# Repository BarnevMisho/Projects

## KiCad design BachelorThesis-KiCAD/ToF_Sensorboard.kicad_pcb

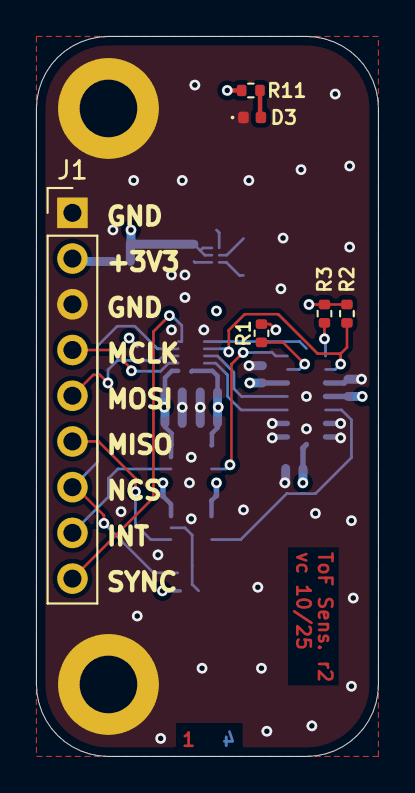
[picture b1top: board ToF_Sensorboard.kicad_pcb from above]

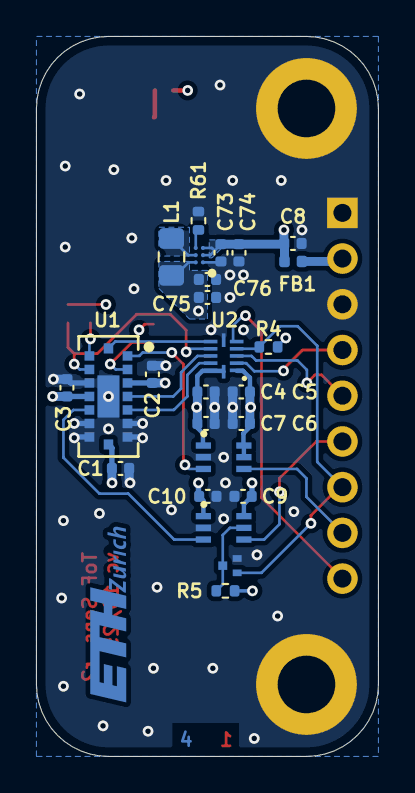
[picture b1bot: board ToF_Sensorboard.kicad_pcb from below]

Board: 4 copper layers, 19.0 x 40.0 mm, 34 parts (26 on the bottom side), 22 nets.

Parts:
A1: eth-zurich_2mm
C1, C2, C4, C5, C6, C7, C9, C10: 100n; C_0402_1005Metric
C3, C8: 4u7; C_0402_1005Metric
C73, C74, C75, C76: 10u; C_0402_1005Metric
D3: LED GREEN; LED_0402_1005Metric
FB1: BLM15AG102SH1J; L_0402_1005Metric
H1, H2: MountingHole_Pad; MountingHole_3.2mm_M3_DIN965_Pad
J1: Conn_01x09_Pin; PinHeader_1x09_P2.54mm_Vertical
L1: 2u2; L_0805_2012Metric_Pad1.15x1.40mm_HandSolder
Q1: RUM001L02T2CL
R1, R2, R3, R4, R5: 47k; R_0402_1005Metric
R11: 680R; R_0402_1005Metric
R61: 0R; R_0402_1005Metric
U1: VL53L8CXV0GC/1; VL53L8CXV0GC
U2: TXU0104RUTR; PQFP12_RUT_TEX-L
U3, U4: TXU0101DCKR; SC70-6_DCK_TEX
U20: TPS62840YBGR

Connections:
+1V8: C1.1, C2.1, C4.1, C7.1, C10.1, C75.1, C76.1, L1.2, R1.1, R2.1, R3.1, U1.A3 (IOVDD), U1.B7 (CORE_1V8), U2.11 (VCCB), U2.12 (OE), U3.1 (VCCA), U4.1 (VCCA), U20.A2 (VOS)
+3.3VA: C3.1, C5.1, C6.1, C8.1, C9.1, C73.1, C74.1, FB1.2, R4.1, R5.1, R11.1, U1.C4 (AVDD), U2.1 (VCCA), U3.5 (OE), U3.6 (VCCB), U4.6 (VCCB), U20.B1 (VIN), U20.C1 (EN)
/INT: J1.8, U3.4 (BY)
/INT_1V8: U1.A1 (GPIO1/INT), U3.3 (A)
/MCLK: J1.4, U2.2 (A1)
/MCLK_1V8: U1.A5 (SCL/MCLK), U2.10 (B1Y)
/MISO: J1.6, U4.4 (BY)
/MISO_1V8: U1.C5 (MISO), U4.3 (A)
/MOSI: J1.5, U2.3 (A2)
/MOSI_1V8: U1.A4 (SDA/MOSI), U2.9 (B2Y)
/NCS: J1.7, Q1.1 (Gate), R4.2, U2.4 (A3)
/NCS_1V8: R2.2, U1.C2 (NCS), U2.8 (B3Y)
/SYNC: J1.9, U2.5 (A4)
/SYNC_1V8: U1.B1 (GPIO2/SYNC), U2.7 (B4Y)
GND: C1.2, C2.2, C3.2, C4.2, C5.2, C6.2, C7.2, C8.2, C9.2, C10.2, C73.2, C74.2, C75.2, C76.2, D3.1 (K), H1.1, H2.1, J1.1, J1.3, Q1.2 (Source), R61.2, U1.A6 (RSVD1), U1.A7 (RSVD2), U1.B4 (GND_PAD), U1.C3 (GND), U1.C6 (RSVD3), U1.C7 (GND), U2.6 (GND), U3.2 (GND), U4.2 (GND), U20.A1 (GND)
unnamed: D3.2 (A), R11.2
unnamed: FB1.1, J1.2
unnamed: Q1.3 (Drain), R5.2, U4.5 (OE)
unnamed: R1.2, U1.A2 (LPN)
unnamed: R3.2, U1.C1 (SPI_I2C_N)
unnamed: L1.1, U20.B2 (SW)
unnamed: R61.1, U20.C2 (VSET)

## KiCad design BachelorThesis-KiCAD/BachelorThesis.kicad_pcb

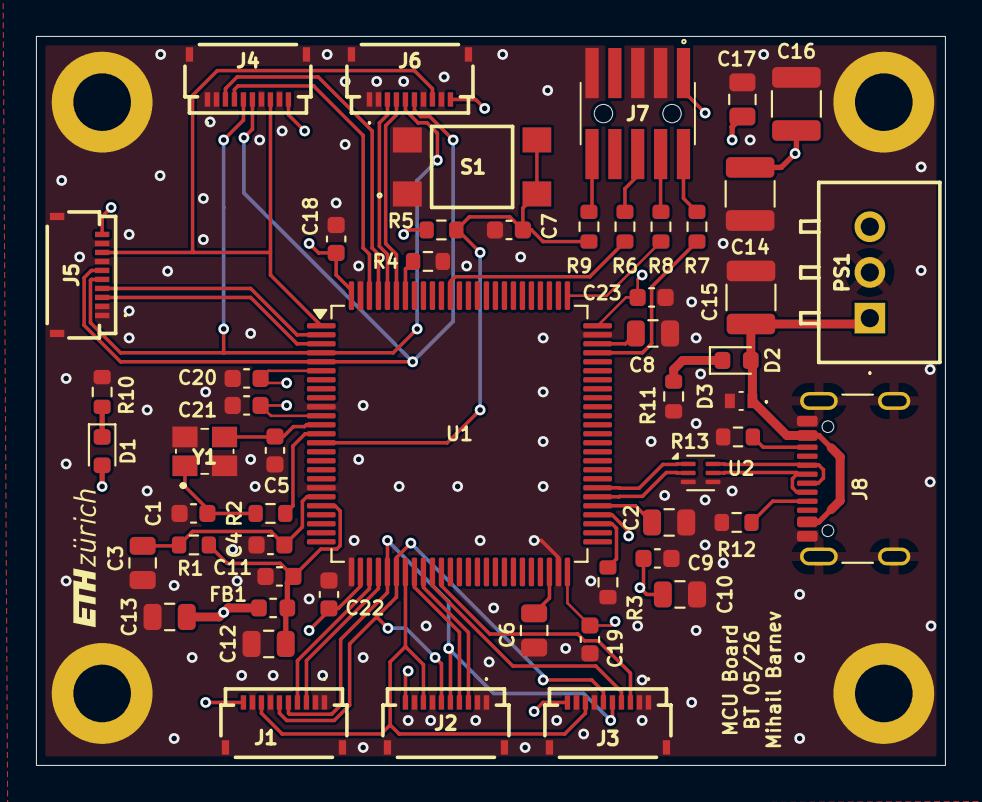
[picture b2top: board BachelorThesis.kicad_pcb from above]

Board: 4 copper layers, 50.5 x 40.5 mm, 57 parts (0 on the bottom side), 47 nets.

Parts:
C1, C5: 10p; C_0603_1608Metric
C2, C6, C8: 2.2u; C_0805_2012Metric
C3, C10, C12, C13: 1u; C_0805_2012Metric
C4, C7, C9, C11, C18, C19, C20, C21, C22, C23: 100n; C_0603_1608Metric
C14, C16: 47u; C_1210_3225Metric
C15: 10u; C_1210_3225Metric
C17: 4.7u; C_0805_2012Metric
D1, D2: LED; LED_0603_1608Metric
D3: ESDA7P60-1U1M; ESDA7P601U1M
FB1: FCM1608KF-601T03 -0603 1608 Metric; L_0603_1608Metric
H1, H2, H3, H4: MountingHole_Pad; MountingHole_3.2mm_M3_DIN965_Pad
J1, J2, J3, J4, J5, J6: FH34SRJ-10S-0.5SH_50_; FH34SRJ10S05SH50
J7: Conn_ARM_JTAG_SWD_10; FTSH-105-XX-YYY-DV-K-A
J8: USB_C_Receptacle_USB2.0_16P; USB_C_Receptacle_GCT_USB4105-xx-A_16P_TopMnt_Horizontal
PS1: TPSM84203EAB
R1, R6, R7, R8, R9: 33ohm; R_0603_1608Metric
R2, R4: 0Ω; R_0603_1608Metric
R3: 3k±1%; R_0603_1608Metric
R5, R12, R13: 5k1±1%; R_0603_1608Metric
R10, R11: 470ohm; R_0603_1608Metric
S1: TL3305AF160QG
U1: STM32F723VET6; LQFP-100_14x14mm_P0.5mm
U2: ECMF02-2AMX6; ST_UQFN-6L_1.5x1.7mm_P0.5mm
Y1: ABM8W-25.0000MHZ-8-D1X-T3; ABM8W480000MHZ6D1XT3

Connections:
/MCU_CORE/HSE_IN: C5.1 (+), U1.12 (PH0), Y1.3 (X2)
/MCU_CORE/HSE_OUT: R2.1 (+), U1.13 (PH1)
/MCU_CORE/INT_1_1: J1.3, U1.29 (PA5)
/MCU_CORE/INT_1_2: J2.3, U1.34 (PB0)
/MCU_CORE/INT_1_3: J3.3, U1.36 (PB2)
/MCU_CORE/INT_4_1: J4.3, U1.97 (PE0)
/MCU_CORE/INT_4_2: J5.3, U1.3 (PE4)
/MCU_CORE/INT_4_3: J6.3, U1.96 (PB9)
/MCU_CORE/NCS_1_1: J1.4, U1.28 (PA4)
/MCU_CORE/NCS_1_2: J2.4, U1.33 (PC5)
/MCU_CORE/NCS_1_3: J3.4, U1.35 (PB1)
/MCU_CORE/NCS_4_1: J4.4, U1.98 (PE1)
/MCU_CORE/NCS_4_2: J5.4, U1.2 (PE3)
/MCU_CORE/NCS_4_3: J6.4, U1.95 (PB8)
/MCU_CORE/SPI1_MISO: J1.5, J2.5, J3.5, U1.30 (PA6)
/MCU_CORE/SPI1_MOSI: J1.6, J2.6, J3.6, U1.31 (PA7)
/MCU_CORE/SPI1_SCK: J1.8, J2.8, J3.8, U1.32 (PC4)
/MCU_CORE/SPI4_MISO: J4.5, J5.5, J6.5, U1.4 (PE5)
/MCU_CORE/SPI4_MOSI: J4.6, J5.6, J6.6, U1.5 (PE6)
/MCU_CORE/SPI4_SCK: J4.8, J5.8, J6.8, U1.1 (PE2)
/MCU_CORE/SWD_CLK: J7.4 (SWCLK/TCK), R8.2 (-)
/MCU_CORE/SWD_DIO: J7.2 (SWDIO/TMS), R7.2 (-)
/MCU_CORE/SWD_NRST: C7.2 (-), R5.2, R9.1 (+), S1.2, S1.4, U1.14 (NRST)
/MCU_CORE/SWD_SWO: J7.6 (SWO/TDO), R6.2 (-)
/MCU_CORE/USBC_N: J8.A7 (D-), J8.B7 (D-), U2.5 (D-_out)
/MCU_CORE/USBC_P: J8.A6 (D+), J8.B6 (D+), U2.6 (D+_out)
/MCU_CORE/USB_HS_N: U1.56 (PB14), U2.2 (D-_in)
/MCU_CORE/USB_HS_P: U1.57 (PB15), U2.1 (D+_in)
GND: C1.2 (-), C2.2 (-), C3.2 (-), C4.2 (-), C5.2 (-), C6.2 (-), C7.1 (+), C8.2 (-), C9.2 (-), C10.2 (-), C11.2 (-), C12.2 (-), C13.2 (-), C14.2 (-), C15.1 (+), C16.2 (-), C17.2 (-), C18.2 (-), C19.2 (-), C20.2 (-), C21.2 (-), C22.2 (-), C23.2 (-), D3.2 (A), H1.1, H2.1, H3.1, H4.1, J1.1, J1.2, J1.7, J1.9, J1.11 (MP1), J1.12 (MP2), J2.1, J2.2, J2.7, J2.9, J2.11 (MP1), J2.12 (MP2), J3.1, J3.2, J3.7, J3.9, J3.11 (MP1), J3.12 (MP2), J4.1, J4.2, J4.7, J4.9, J4.11 (MP1), J4.12 (MP2), J5.1, J5.2, J5.7, J5.9, J5.11 (MP1), J5.12 (MP2), J6.1, J6.2, J6.7, J6.9, J6.11 (MP1), J6.12 (MP2), J7.3 (GND), J7.5 (GND), J7.9 (GNDDetect), J8.A1 (GND), J8.A12 (GND), J8.B1 (GND), J8.B12 (GND), J8.S1 (SHIELD), PS1.2 (GND), R3.2 (-), R4.2 (-), R10.2 (-), R11.1 (+), R12.1 (+), R13.1 (+), S1.1, S1.3, U1.10 (VSS), U1.19 (VSSA), U1.26 (VSS), U1.49 (VSS), U1.74 (VSS), U1.99 (VSS), U2.3 (GND), U2.4 (NC), Y1.2 (GND_1), Y1.4 (GND_2)
unnamed: C1.1 (+), R2.2 (-), Y1.1 (X1)
unnamed: C2.1 (+), U1.55 (V12PHYHS)
unnamed: C6.1 (+), U1.48 (VCAP_1)
unnamed: C8.1 (+), U1.73 (VCAP_2)
unnamed: D1.1 (K), R10.1 (+)
unnamed: D2.1 (K), R11.2 (-)
unnamed: J7.10 (~RESET), R9.2 (-)
unnamed: J8.A5 (CC1), R12.2 (-)
unnamed: J8.B5 (CC2), R13.2 (-)
unnamed: R3.1 (+), U1.53 (REXTPHYHS)
unnamed: R4.1 (+), U1.94 (BOOT0)
unnamed: R6.1 (+), U1.89 (PB3)
unnamed: R7.1 (+), U1.72 (PA13)
unnamed: R8.1 (+), U1.76 (PA14)
VBUS: C15.2 (-), D2.2 (A), D3.1 (K), J8.A4 (VBUS), J8.A9 (VBUS), J8.B4 (VBUS), J8.B9 (VBUS), PS1.1 (VIN)
VDD: C9.1 (+), C10.1 (+), C13.1 (+), C14.1 (+), C16.1 (+), C17.1 (+), C18.1 (+), C19.1 (+), C20.1 (+), C21.1 (+), C22.1 (+), C23.1 (+), D1.2 (A), FB1.2, J1.10, J2.10, J3.10, J4.10, J5.10, J6.10, J7.1 (VTref), PS1.3 (VOUT), R5.1, U1.6 (VBAT), U1.11 (VDD), U1.27 (VDD), U1.50 (VDD), U1.54 (VDDPHYHS), U1.75 (VDD), U1.100 (VDD)
VDDA: C11.1 (+), C12.1 (+), FB1.1, R1.1 (+), U1.21 (VDDA)
VREF+: C3.1 (+), C4.1 (+), R1.2 (-), U1.20 (VREF+)

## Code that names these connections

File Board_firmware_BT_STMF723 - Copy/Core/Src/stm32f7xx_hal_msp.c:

/* USER CODE BEGIN Header */
/**
  ******************************************************************************
  * @file         stm32f7xx_hal_msp.c
  * @brief        This file provides code for the MSP Initialization
  *               and de-Initialization codes.
  ******************************************************************************
  * @attention
  *
  * Copyright (c) 2026 STMicroelectronics.
  * All rights reserved.
  *
  * This software is licensed under terms that can be found in the LICENSE file
  * in the root directory of this software component.
  * If no LICENSE file comes with this software, it is provided AS-IS.
  *
  ******************************************************************************
  */
/* USER CODE END Header */
/* Includes ------------------------------------------------------------------*/
#include "main.h"
/* USER CODE BEGIN Includes */

/* USER CODE END Includes */

/* Private typedef -----------------------------------------------------------*/
/* USER CODE BEGIN TD */

/* USER CODE END TD */

/* Private define ------------------------------------------------------------*/
/* USER CODE BEGIN Define */

/* USER CODE END Define */

/* Private macro -------------------------------------------------------------*/
/* USER CODE BEGIN Macro */

/* USER CODE END Macro */

/* Private variables ---------------------------------------------------------*/
/* USER CODE BEGIN PV */

/* USER CODE END PV */

/* Private function prototypes -----------------------------------------------*/
/* USER CODE BEGIN PFP */

/* USER CODE END PFP */

/* External functions --------------------------------------------------------*/
/* USER CODE BEGIN ExternalFunctions */

/* USER CODE END ExternalFunctions */

/* USER CODE BEGIN 0 */

/* USER CODE END 0 */
/**
  * Initializes the Global MSP.
  */
void HAL_MspInit(void)
{

  /* USER CODE BEGIN MspInit 0 */

  /* USER CODE END MspInit 0 */

  __HAL_RCC_PWR_CLK_ENABLE();
  __HAL_RCC_SYSCFG_CLK_ENABLE();

  /* System interrupt init*/

  /* USER CODE BEGIN MspInit 1 */

  /* USER CODE END MspInit 1 */
}

/**
  * @brief SPI MSP Initialization
  * This function configures the hardware resources used in this example
  * @param hspi: SPI handle pointer
  * @retval None
  */
void HAL_SPI_MspInit(SPI_HandleTypeDef* hspi)
{
  GPIO_InitTypeDef GPIO_InitStruct = {0};
  if(hspi->Instance==SPI1)
  {
    /* USER CODE BEGIN SPI1_MspInit 0 */

    /* USER CODE END SPI1_MspInit 0 */
    /* Peripheral clock enable */
    __HAL_RCC_SPI1_CLK_ENABLE();

    __HAL_RCC_GPIOA_CLK_ENABLE();
    /**SPI1 GPIO Configuration
    PA5     ------> SPI1_SCK
    PA6     ------> SPI1_MISO
    PA7     ------> SPI1_MOSI
    */
    GPIO_InitStruct.Pin = GPIO_PIN_5|GPIO_PIN_6|GPIO_PIN_7;
    GPIO_InitStruct.Mode = GPIO_MODE_AF_PP;
    GPIO_InitStruct.Pull = GPIO_NOPULL;
    GPIO_InitStruct.Speed = GPIO_SPEED_FREQ_VERY_HIGH;
    GPIO_InitStruct.Alternate = GPIO_AF5_SPI1;
    HAL_GPIO_Init(GPIOA, &GPIO_InitStruct);

    /* USER CODE BEGIN SPI1_MspInit 1 */

    /* USER CODE END SPI1_MspInit 1 */
  }
  else if(hspi->Instance==SPI4)
  {
    /* USER CODE BEGIN SPI4_MspInit 0 */

    /* USER CODE END SPI4_MspInit 0 */
    /* Peripheral clock enable */
    __HAL_RCC_SPI4_CLK_ENABLE();

    __HAL_RCC_GPIOE_CLK_ENABLE();
    /**SPI4 GPIO Configuration
    PE2     ------> SPI4_SCK
    PE5     ------> SPI4_MISO
    PE6     ------> SPI4_MOSI
    */
    GPIO_InitStruct.Pin = GPIO_PIN_2|GPIO_PIN_5|GPIO_PIN_6;
    GPIO_InitStruct.Mode = GPIO_MODE_AF_PP;
    GPIO_InitStruct.Pull = GPIO_NOPULL;
    GPIO_InitStruct.Speed = GPIO_SPEED_FREQ_VERY_HIGH;
    GPIO_InitStruct.Alternate = GPIO_AF5_SPI4;
    HAL_GPIO_Init(GPIOE, &GPIO_InitStruct);

    /* USER CODE BEGIN SPI4_MspInit 1 */

    /* USER CODE END SPI4_MspInit 1 */
  }

}

/**
  * @brief SPI MSP De-Initialization
  * This function freeze the hardware resources used in this example
  * @param hspi: SPI handle pointer
  * @retval None
  */
void HAL_SPI_MspDeInit(SPI_HandleTypeDef* hspi)
{
  if(hspi->Instance==SPI1)
  {
    /* USER CODE BEGIN SPI1_MspDeInit 0 */

    /* USER CODE END SPI1_MspDeInit 0 */
    /* Peripheral clock disable */
    __HAL_RCC_SPI1_CLK_DISABLE();

    /**SPI1 GPIO Configuration
    PA5     ------> SPI1_SCK
    PA6     ------> SPI1_MISO
    PA7     ------> SPI1_MOSI
    */
    HAL_GPIO_DeInit(GPIOA, GPIO_PIN_5|GPIO_PIN_6|GPIO_PIN_7);

    /* USER CODE BEGIN SPI1_MspDeInit 1 */

    /* USER CODE END SPI1_MspDeInit 1 */
  }
  else if(hspi->Instance==SPI4)
  {
    /* USER CODE BEGIN SPI4_MspDeInit 0 */

    /* USER CODE END SPI4_MspDeInit 0 */
    /* Peripheral clock disable */
    __HAL_RCC_SPI4_CLK_DISABLE();

    /**SPI4 GPIO Configuration
    PE2     ------> SPI4_SCK
    PE5     ------> SPI4_MISO
    PE6     ------> SPI4_MOSI
    */
    HAL_GPIO_DeInit(GPIOE, GPIO_PIN_2|GPIO_PIN_5|GPIO_PIN_6);

    /* USER CODE BEGIN SPI4_MspDeInit 1 */

    /* USER CODE END SPI4_MspDeInit 1 */
  }

}

/* USER CODE BEGIN 1 */

/* USER CODE END 1 */

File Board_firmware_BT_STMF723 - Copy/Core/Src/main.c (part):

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// hardware interrupt callback function
void HAL_GPIO_EXTI_Callback(uint16_t GPIO_Pin)
{
    if(GPIO_Pin == INT_4_1_Pin) {data_ready_4_1 = 1;}
    if(GPIO_Pin == INT_4_2_Pin) {data_ready_4_2 = 1;}
    if(GPIO_Pin == INT_4_3_Pin) {data_ready_4_3 = 1;}
}
/* USER CODE END 0 */

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	// SENSOR 4_1 CONFIGURATION (SPI 4)
	// ==========================================
	tof4_1.platform.hspi = &hspi4;
	tof4_1.platform.ncs_gpio_port = NCS_4_1_GPIO_Port;
	tof4_1.platform.ncs_pin = NCS_4_1_Pin;

	vl53l8cx_set_power_mode(&tof4_1, VL53L8CX_POWER_MODE_DEEP_SLEEP);
	VL53L8CX_Reset_Sensor(&tof4_1.platform);
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	// SENSOR 4_2 CONFIGURATION (SPI 4)
	// ==========================================
	tof4_2.platform.hspi = &hspi4;
	tof4_2.platform.ncs_gpio_port = NCS_4_2_GPIO_Port;
	tof4_2.platform.ncs_pin = NCS_4_2_Pin;

	vl53l8cx_set_power_mode(&tof4_2, VL53L8CX_POWER_MODE_DEEP_SLEEP);
	VL53L8CX_Reset_Sensor(&tof4_2.platform);
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	// SENSOR 4_3 CONFIGURATION (SPI 4)
	// ==========================================
	tof4_3.platform.hspi = &hspi4;
	tof4_3.platform.ncs_gpio_port = NCS_4_3_GPIO_Port;
	tof4_3.platform.ncs_pin = NCS_4_3_Pin;

	vl53l8cx_set_power_mode(&tof4_3, VL53L8CX_POWER_MODE_DEEP_SLEEP);
	VL53L8CX_Reset_Sensor(&tof4_3.platform);
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	// SENSOR 1_1 CONFIGURATION (SPI 1)
	// ==========================================
	tof1_1.platform.hspi = &hspi1; // Using SPI1
	tof1_1.platform.ncs_gpio_port = NCS_1_1_GPIO_Port;
	tof1_1.platform.ncs_pin = NCS_1_1_Pin;

	vl53l8cx_set_power_mode(&tof1_1, VL53L8CX_POWER_MODE_DEEP_SLEEP);
	VL53L8CX_Reset_Sensor(&tof1_1.platform);
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	// SENSOR 1_2 CONFIGURATION (SPI 1)
	// ==========================================
	tof1_2.platform.hspi = &hspi1;
	tof1_2.platform.ncs_gpio_port = NCS_1_2_GPIO_Port;
	tof1_2.platform.ncs_pin = NCS_1_2_Pin;

	vl53l8cx_set_power_mode(&tof1_2, VL53L8CX_POWER_MODE_DEEP_SLEEP);
	VL53L8CX_Reset_Sensor(&tof1_2.platform);
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	// SENSOR 1_3 CONFIGURATION (SPI 1)
	// ==========================================
	tof1_3.platform.hspi = &hspi1;
	tof1_3.platform.ncs_gpio_port = NCS_1_3_GPIO_Port;
	tof1_3.platform.ncs_pin = NCS_1_3_Pin;

	vl53l8cx_set_power_mode(&tof1_3, VL53L8CX_POWER_MODE_DEEP_SLEEP);
	VL53L8CX_Reset_Sensor(&tof1_3.platform);
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  __HAL_RCC_GPIOB_CLK_ENABLE();

  /*Configure GPIO pin Output Level */
  HAL_GPIO_WritePin(GPIOE, NCS_4_2_Pin|NCS_4_1_Pin, GPIO_PIN_SET);

  /*Configure GPIO pin Output Level */
  HAL_GPIO_WritePin(NCS_1_1_GPIO_Port, NCS_1_1_Pin, GPIO_PIN_SET);

  /*Configure GPIO pin Output Level */
  HAL_GPIO_WritePin(NCS_1_2_GPIO_Port, NCS_1_2_Pin, GPIO_PIN_SET);

  /*Configure GPIO pin Output Level */
  HAL_GPIO_WritePin(GPIOB, NCS_1_3_Pin|NCS_4_3_Pin, GPIO_PIN_SET);

  /*Configure GPIO pins : NCS_4_2_Pin NCS_4_1_Pin */
  GPIO_InitStruct.Pin = NCS_4_2_Pin|NCS_4_1_Pin;
  GPIO_InitStruct.Mode = GPIO_MODE_OUTPUT_PP;
  GPIO_InitStruct.Pull = GPIO_NOPULL;
  GPIO_InitStruct.Speed = GPIO_SPEED_FREQ_HIGH;
  HAL_GPIO_Init(GPIOE, &GPIO_InitStruct);

  /*Configure GPIO pins : INT_4_2_Pin INT_4_1_Pin */
  GPIO_InitStruct.Pin = INT_4_2_Pin|INT_4_1_Pin;
  GPIO_InitStruct.Mode = GPIO_MODE_IT_FALLING;
  GPIO_InitStruct.Pull = GPIO_NOPULL;
  HAL_GPIO_Init(GPIOE, &GPIO_InitStruct);

  /*Configure GPIO pin : NCS_1_1_Pin */
  GPIO_InitStruct.Pin = NCS_1_1_Pin;
  GPIO_InitStruct.Mode = GPIO_MODE_OUTPUT_PP;
  GPIO_InitStruct.Pull = GPIO_NOPULL;
  GPIO_InitStruct.Speed = GPIO_SPEED_FREQ_HIGH;
  HAL_GPIO_Init(NCS_1_1_GPIO_Port, &GPIO_InitStruct);

  /*Configure GPIO pin : NCS_1_2_Pin */
  GPIO_InitStruct.Pin = NCS_1_2_Pin;
  GPIO_InitStruct.Mode = GPIO_MODE_OUTPUT_PP;
  GPIO_InitStruct.Pull = GPIO_NOPULL;
  GPIO_InitStruct.Speed = GPIO_SPEED_FREQ_HIGH;
  HAL_GPIO_Init(NCS_1_2_GPIO_Port, &GPIO_InitStruct);

  /*Configure GPIO pins : NCS_1_3_Pin NCS_4_3_Pin */
  GPIO_InitStruct.Pin = NCS_1_3_Pin|NCS_4_3_Pin;
  GPIO_InitStruct.Mode = GPIO_MODE_OUTPUT_PP;
  GPIO_InitStruct.Pull = GPIO_NOPULL;
  GPIO_InitStruct.Speed = GPIO_SPEED_FREQ_HIGH;
  HAL_GPIO_Init(GPIOB, &GPIO_InitStruct);

  /*Configure GPIO pin : INT_4_3_Pin */
  GPIO_InitStruct.Pin = INT_4_3_Pin;
  GPIO_InitStruct.Mode = GPIO_MODE_IT_FALLING;
  GPIO_InitStruct.Pull = GPIO_NOPULL;
  HAL_GPIO_Init(INT_4_3_GPIO_Port, &GPIO_InitStruct);

  /* EXTI interrupt init*/
  HAL_NVIC_SetPriority(EXTI0_IRQn, 0, 0);
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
